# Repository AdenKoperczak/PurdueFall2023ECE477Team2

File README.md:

# PurdueFall2023ECE477Team2
Code and other files for a desktop Skee-Ball Machine. Our team website can be
found at [https://engineering.purdue.edu/477grp2/](https://engineering.purdue.edu/477grp2/).

# Purdue ECE47700 - Digital Systems Senior Project
This class involves designing a electronics project that could be sold as a 
product. Such a product must involve either a microcontroller or FPGA. More
information can be found at [https://engineering.purdue.edu/ece477/](https://engineering.purdue.edu/ece477/).

# Git Folders and Files
The files in our Git Repository can be broken into two sections: electrical and
code. Electrical design was done in KiCAD 7.0 and includes both schematics and
PCB layouts. Code was done using SystemWorkbench. There are also some other 
code and support files. Bellow is a description of each folder and what it
contains along with some soport files files.

## General Files
- Used Resources.txt: This contains what parts of the microcontroller are being
                      used for what.

## Electrical
- Audio AMP: Contains initial design for our audio amplifier.
- Schematic: Contains the overall schematic and PCB for our design.
- power control: Contains the initial design for our power circuitry.
- sensor: Contains the initial design for our laser break circuit.

## Microcontroller Code
- HUB75Lib: This contains a library and test code to run a 32x64 HUB75 display
            including a font library.
- WS2812BLib: This contains a library and test code for running a WS2812B LED strip.
- SoundLib: This contains a library and test code for generating and playing audio.

## Other Code
- HUB75Font\_Generate: This contains code for generating a font library for the
                       HUB75Lib.

# Project Description
Our project aims to rekindle the nostalgic joy of the traditional Skee-Ball game while
incorporating cutting-edge technology for an enhanced playing experience in the form of
game modes, normal, time attack, and streak. The normal game mode is the same 
as the traditional skate-ball game mode, such that a player would get nine balls and attempt
to score the highest score possible at their own pace, for which the scores per ball are
simply added to get the final score. After they run out of nine balls, any ball they try
to score after would not count, as the game would be over. In time attack mode, the
player sets a time (up to 5 minutes) with an unlimited ball count to score as high as
possible. For the streak mode, the player gets an "unlimited" number of balls as long as
as they score 20 points or higher on the current shot; Once they miss the shot, the score
is finalized. Finally, the timed streak mode combines the time attack with a score.
multiplier, which will go up by 0.1x from 1x every time they make the shot, maxing out at
1.5x and indicated by an LED light bar to the player. Once the player misses a 20+
point shot, the multiplier is reset. The Skee-Ball Machine" is similar to other arcade
machines that you can easily see in arcades; however, they are unaffordable to buy and
are huge in size. Therefore, we specifically designed it to be portable and affordable. 
To make it portable, we replaced the rolling rail into bouncing pad, so the player will 
score the ball by throwing the ball off of the bouncing pad. This device will use a microcontroller,
along with several sensors, buttons, displays, and a speaker to make an iterative game with
different scoring modes to keep the game fresh. In detail, sensors will detect the ball
once they are scored. Also, there will be a speaker, so it will have certain game effects.
sounds when scored through a user-defined amplifier. Also, there will be a display for user 
interfaces to show the score and how much time is left. Finally, we will create a power regulator
to regulate the power supply. We will use a commercial 12V power supply because our speaker 
requires 12V, then we will implement a voltage regulator (buck converter) from 12V commercial 
voltage input to 5V to supply our display, and another linear regulator from 5V to 3.3V to 
supply microprocessors and other components.

## Stretch Goal:
An ability to implement a WS2812B LED-strip to generate some flashing light as a game effect, 
using GPIO pins to operate and a PWM to adjust brightness and frequency to generate certain effect.

## Project Specific Design Requirements (PSDRs):
- PSDR #1 (Hardware): An ability to implement one 32-by-64 column-row
                      matrix display to interface with user, by communicating through GPIO
                      pins from microcontroller. 
- PSDR #2 (Hardware): An ability to implement one 4-by-4 column-row
                      matrix keypad to receive user's input, by communicating through GPIO
                      pins from microcontroller.
- PSDR #3 (Hardware): An ability to generate a soundwave using DAC 
                      from microcontroller and amplify the signal using a user designed
                      audio amplifier to play game effect sounds through a speaker.
- PSDR #4 (Hardware): An ability to implement a step down voltage
                      regulator(buck converter) from 12V commercial voltage input to 5V, and
                      another linear regulator from 5V to 3.3V as we need both 5V and 3.3V
                      to supply different components.
- PSDR #5 (Software): An ability to implement the game logic using system
                      workbench for STM32(eclipse), to properly implement all components, such
                      as optical sensor, display, keypad, and speaker.

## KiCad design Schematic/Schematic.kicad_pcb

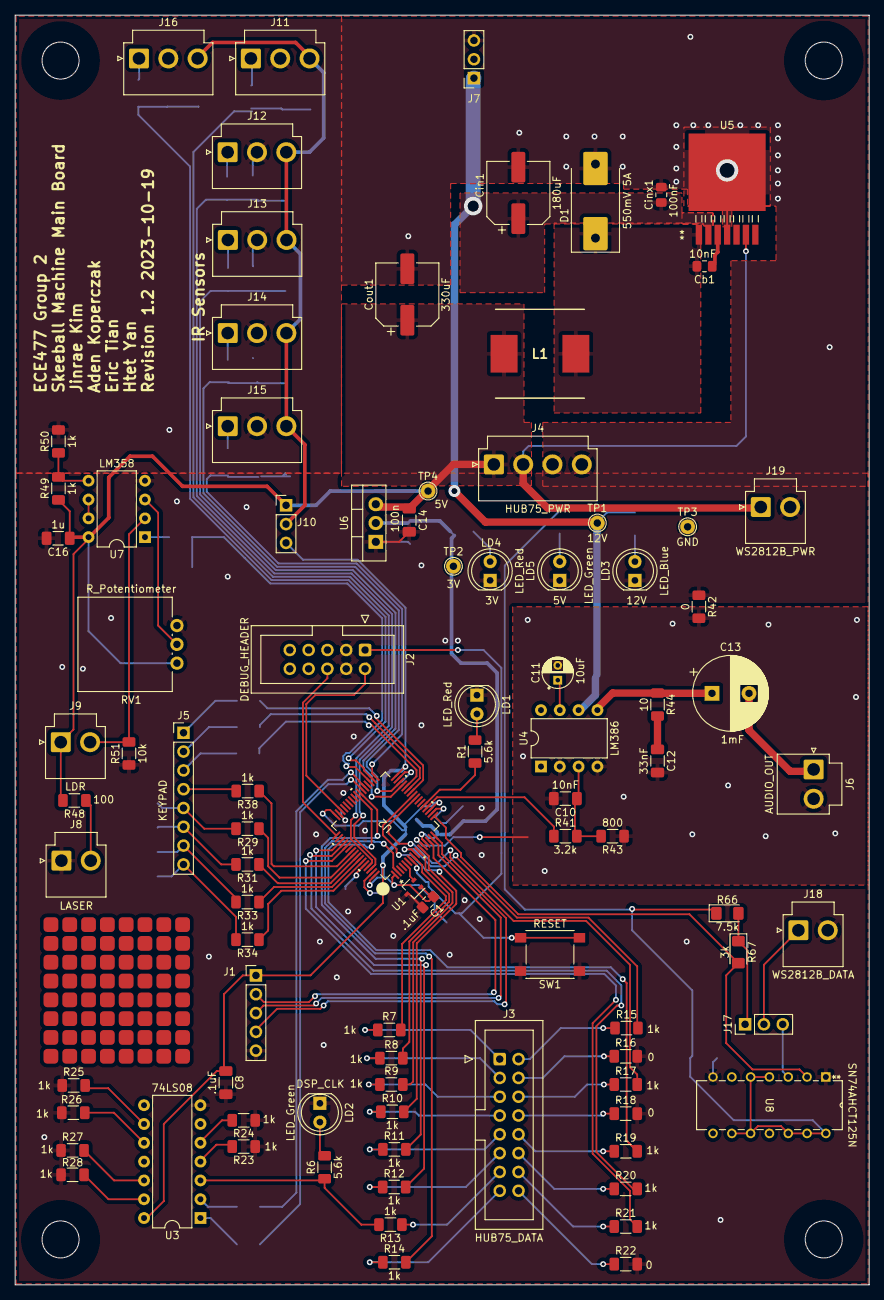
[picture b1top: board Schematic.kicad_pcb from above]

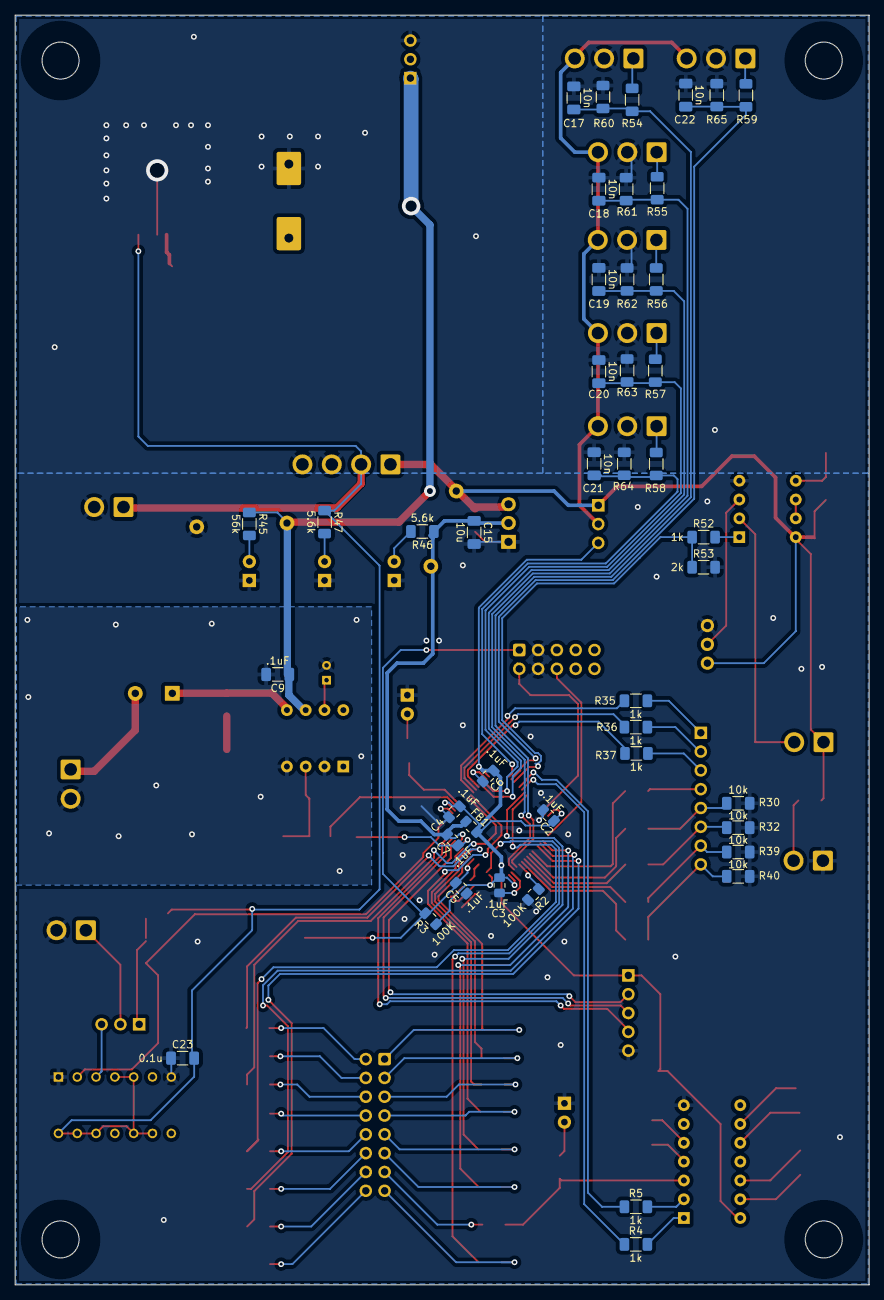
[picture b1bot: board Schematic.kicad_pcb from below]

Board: 2 copper layers, 115.3 x 171.4 mm, 139 parts (44 on the bottom side), 107 nets.

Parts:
C1, C2, C3, C4, C5, C6, C7: .1uF; C_0805_2012Metric_Pad1.18x1.45mm_HandSolder
C8, C9: .1uF; C_1206_3216Metric_Pad1.33x1.80mm_HandSolder
C10: 10nF; C_1206_3216Metric_Pad1.33x1.80mm_HandSolder
C11: 10uF; CP_Radial_D4.0mm_P2.00mm
C12: 33nF; C_1206_3216Metric_Pad1.33x1.80mm_HandSolder
C13: 1mF; CP_Radial_D10.0mm_P5.00mm
C14: 100n; C_1206_3216Metric_Pad1.33x1.80mm_HandSolder
C15: 10u; C_1206_3216Metric_Pad1.33x1.80mm_HandSolder
C16: 1u; C_1206_3216Metric_Pad1.33x1.80mm_HandSolder
C17, C18, C19, C20, C21, C22: 10n; C_1206_3216Metric_Pad1.33x1.80mm_HandSolder
C23: 0.1u; C_1206_3216Metric_Pad1.33x1.80mm_HandSolder
Cb1: 10nF; C_0805_2012Metric_Pad1.18x1.45mm_HandSolder
Cin1: 180uF; CP_Elec_8x6.9
Cinx1: 100nF; C_0805_2012Metric_Pad1.18x1.45mm_HandSolder
Cout1: 330uF; CP_Elec_8x6.9
D1: 550mV 5A; D_SMC-RM10_Universal_Handsoldering
FB1: Ferrite Bead; L_0805_2012Metric_Pad1.15x1.40mm_HandSolder
H1, H2, H3, H4: MountingHole; MountingHole_5mm
J1: Conn_01x05_Pin; PinHeader_1x05_P2.54mm_Vertical
J2: DEBUG_HEADER; IDC-Header_2x05_P2.54mm_Vertical
J3: HUB75_DATA; IDC-Header_2x08_P2.54mm_Vertical
J4: HUB75_PWR; JST_VH_B4P-VH-B_1x04_P3.96mm_Vertical
J5: KEYPAD; PinHeader_1x08_P2.54mm_Vertical
J6: AUDIO_OUT; JST_VH_B2P-VH-B_1x02_P3.96mm_Vertical
J7: Conn_01x03_Pin; PinSocket_1x03_P2.54mm_Vertical
J8: LASER; JST_VH_B2P-VH-B_1x02_P3.96mm_Vertical
J9: LDR; JST_VH_B2P-VH-B_1x02_P3.96mm_Vertical
J10, J17: Conn_01x03_Pin; PinHeader_1x03_P2.54mm_Vertical
J11, J12, J13, J14, J15, J16: Conn_01x03_Pin; JST_VH_B3P-VH_1x03_P3.96mm_Vertical
J18: WS2812B_DATA; JST_VH_B2P-VH-B_1x02_P3.96mm_Vertical
J19: WS2812B_PWR; JST_VH_B2P-VH-B_1x02_P3.96mm_Vertical
L1: 10uH; INDPM120120X1020N
LD1, LD4: LED_Red; LED_D5.0mm
LD2, LD5: LED_Green; LED_D5.0mm
LD3: LED_Blue; LED_D5.0mm
R1, R6, R46, R47: 5.6k; R_1206_3216Metric_Pad1.30x1.75mm_HandSolder
R2, R3: 100K; C_0805_2012Metric_Pad1.18x1.45mm_HandSolder
R4, R5, R7, R8, R9, R10, R11, R12, R13, R14, R15, R17, R19, R20, R21, R23, R24, R25, R26, R27, R28, R29, R31, R33, R34, R35, R36, R37, R38, R49, R50, R52, R54, R55, R56, R57, R58, R59: 1k; R_1206_3216Metric_Pad1.30x1.75mm_HandSolder
R16, R18, R22, R42: 0; R_1206_3216Metric_Pad1.30x1.75mm_HandSolder
R30, R32, R39, R40, R51: 10k; R_1206_3216Metric_Pad1.30x1.75mm_HandSolder
R41: 3.2k; R_1206_3216Metric_Pad1.30x1.75mm_HandSolder
R43: 800; R_1206_3216Metric_Pad1.30x1.75mm_HandSolder
R44: 10; R_1206_3216Metric_Pad1.30x1.75mm_HandSolder
R45: 56k; R_1206_3216Metric_Pad1.30x1.75mm_HandSolder
R48: 100; R_1206_3216Metric_Pad1.30x1.75mm_HandSolder
R53, R60, R61, R62, R63, R64, R65: 2k; R_1206_3216Metric_Pad1.30x1.75mm_HandSolder
R66: 7.5k; LED_1206_3216Metric_Pad1.42x1.75mm_HandSolder
R67: 3k; LED_1206_3216Metric_Pad1.42x1.75mm_HandSolder
RV1: R_Potentiometer; Potentiometer_Vishay_148-149_Single_Vertical
SW1: RESET; SW_SPST_PTS645
TP1: 12V; TestPoint_THTPad_D2.0mm_Drill1.0mm
TP2: 3V; TestPoint_THTPad_D2.0mm_Drill1.0mm
TP3: GND; TestPoint_THTPad_D2.0mm_Drill1.0mm
TP4: 5V; TestPoint_THTPad_D2.0mm_Drill1.0mm
U1: MAX7375AXR805; SOT-323_SC-70
U2: STM32F091RCT6; LQFP64-10x10mm_STM
U3: 74LS08; DIP-14_W7.62mm
U4: LM386; DIP-8_W7.62mm
U5: LM2678S-12; TS7B
U6: LD1117S33TR_SOT223; TO-220-3_Vertical
U7: LM358; DIP-8_W7.62mm
U8: SN74AHCT125N; N14

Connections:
+3V0: C1.1, C2.1, C3.1, C4.1, C6.1, C8.1, FB1.2, J1.1, J10.3, R3.1, U1.1 (V+), U2.1 (VBAT), U2.19 (VDD), U2.32 (VDD), U2.48 (VDDIO2), U2.64 (VDD), U3.14 (VCC)
+5V: C14.1, C16.1, C23.2, Cout1.1, J4.1, J4.2, J9.1, J10.1, J19.1, L1.2, R47.1, R48.2, R49.1, R66.1, RV1.3, TP4.1, U5.6 (FB), U6.3 (VI), U7.8 (V+), U8.4 (*2OE), U8.5 (2A), U8.9 (3A), U8.10 (*3OE), U8.12 (4A), U8.13 (*4OE), U8.14 (VCC)
+12V: C9.1, Cin1.1, Cinx1.1, J7.1, R45.1, TP1.1, U4.6 (V+), U5.2 (VIN)
/Sensors/Vsens: J10.2, J11.3, J12.3, J13.3, J14.3, J15.3, J16.3
/WS2812B/WS_DATA_RES: J17.1, R66.2, R67.1
/WS2812B/WS_DATA_SHIFTER: J17.3, U8.3 (1Y)
/microprocessor/BOOT0: R2.1, U2.60 (PF11-BOOT0)
/microprocessor/NRST: C5.1, J2.1, R3.2, SW1.2, U2.7 (NRST)
/microprocessor/SWCLK_IN: J2.6, U2.49 (PA14)
/microprocessor/SWDIO_IN: J2.2, U2.46 (PA13)
/power/VSW: Cb1.2, D1.1 (K), L1.1, U5.1 (VSW)
GND: C1.2, C2.2, C3.2, C4.2, C5.2, C6.2, C8.2, C14.2, C15.2, C16.2, C17.2, C18.2, C19.2, C20.2, C21.2, C22.2, C23.1, Cin1.2, Cinx1.2, Cout1.2, D1.2 (A), J1.5, J2.3, J2.4, J4.3, J4.4, J7.3, J8.1, J11.2, J12.2, J13.2, J14.2, J15.2, J16.2, J18.2, J19.2, LD1.1 (K), LD2.1 (K), LD3.1 (K), LD4.1 (K), LD5.1 (K), R2.2, R16.2, R18.2, R22.2, R23.1, R24.1, R25.1, R26.1, R27.1, R28.1, R30.1, R32.1, R39.1, R40.1, R42.1, R50.2, R51.1, R53.2, R60.2, R61.2, R62.2, R63.2, R64.2, R65.2, RV1.1, SW1.1, TP3.1, U1.3 (GND), U2.18 (VSS), U2.31 (VSS), U2.47 (VSS), U2.63 (VSS), U3.7 (GND), U5.4 (GND), U5.8 (TAB), U6.1 (GND), U7.4 (V-), U8.1 (*1OE), U8.7 (GND)
GNDA: C7.2, C9.2, C10.2, C11.2, C12.2, J6.2, R42.2, R43.1, U2.12 (VSSA), U4.2 (-), U4.4 (GND)
unnamed: C12.1, R44.2
unnamed: C13.1, R44.1, U4.5
unnamed: J3.1, R7.1
unnamed: J3.2, R15.1
unnamed: J3.3, R8.1
unnamed: J3.4, R16.1
unnamed: J3.5, R9.1
unnamed: J3.6, R17.1
unnamed: J3.7, R10.1
unnamed: J3.8, R18.1
unnamed: J3.9, R11.1
unnamed: J3.10, R19.1
unnamed: J3.11, R12.1
unnamed: J3.12, R20.1
unnamed: J3.13, R13.1
unnamed: J3.14, R21.1
unnamed: J3.15, R14.1
unnamed: J3.16, R22.1
unnamed: J5.1, R35.2
unnamed: J5.2, R36.2
unnamed: J5.3, R37.2
unnamed: J5.4, R38.2
unnamed: J5.5, R29.2, R30.2
unnamed: J5.6, R31.2, R32.2
unnamed: J5.7, R33.2, R39.2
unnamed: J5.8, R34.2, R40.2
unnamed: C13.2, J6.1
unnamed: J8.2, R48.1
unnamed: J9.2, R51.2, U7.2 (-)
unnamed: J11.1, R54.2
unnamed: J12.1, R55.2
unnamed: J13.1, R56.2
unnamed: J14.1, R57.2
unnamed: J15.1, R58.2
unnamed: J16.1, R59.2
unnamed: J17.2, J18.1
unnamed: LD1.2 (A), R1.2
unnamed: LD2.2 (A), R6.2
unnamed: LD3.2 (A), R45.2
unnamed: LD4.2 (A), R46.2
unnamed: LD5.2 (A), R47.2
unnamed: R4.2, U3.1
unnamed: R5.2, U3.2
unnamed: R6.1, R13.2, U3.3
unnamed: R23.2, U3.4
unnamed: R24.2, U3.5
unnamed: R25.2, U3.9
unnamed: R26.2, U3.10
unnamed: R27.2, U3.12
unnamed: R28.2, U3.13
unnamed: R52.2, U7.1
unnamed: U1.2 (CLOCK), U2.5 (PF0-OSC_IN)
unnamed: R1.1, U2.21 (PA5)
unnamed: C10.1, R41.2, R43.2, U4.3 (+)
unnamed: C11.1, U4.7 (BYPASS)
unnamed: Cb1.1, U5.3 (CB)
unnamed: RV1.2, U7.3 (+)
unnamed: R49.2, R50.1, U7.5 (+)
unnamed: U7.6 (-), U7.7
PA0: J1.2, U2.14 (PA0)
PA1: J1.3, U2.15 (PA1)
PA2: J1.4, U2.16 (PA2)
PA3: R67.2, U2.17 (PA3), U8.2 (1A)
PA4: R41.1, U2.20 (PA4)
PB0: R35.1, U2.26 (PB0)
PB1: R36.1, U2.27 (PB1)
PB2: R37.1, U2.28 (PB2)
PB3: R38.1, U2.55 (PB3)
PB4: R29.1, U2.56 (PB4)
PB5: R31.1, U2.57 (PB5)
PB6: R33.1, U2.58 (PB6)
PB7: R34.1, U2.59 (PB7)
PB8: C17.1, R54.1, R60.1, U2.61 (PB8)
PB9: C18.1, R55.1, R61.1, U2.62 (PB9)
PB10: C19.1, R56.1, R62.1, U2.29 (PB10)
PB11: C20.1, R57.1, R63.1, U2.30 (PB11)
PB12: C21.1, R58.1, R64.1, U2.33 (PB12)
PB13: C22.1, R59.1, R65.1, U2.34 (PB13)
PB14: R52.1, R53.1, U2.35 (PB14)
PC0: R7.2, U2.8 (PC0)
PC1: R15.2, U2.9 (PC1)
PC2: R8.2, U2.10 (PC2)
PC3: R9.2, U2.11 (PC3)
PC4: R17.2, U2.24 (PC4)
PC5: R10.2, U2.25 (PC5)
PC6: R5.1, U2.37 (PC6)
PC7: R4.1, U2.38 (PC7)
PC8: R11.2, U2.39 (PC8)
PC9: R19.2, U2.40 (PC9)
PC10: R12.2, U2.51 (PC10)
PC11: R20.2, U2.52 (PC11)
PC12: R21.2, U2.53 (PC12)
PC13: R14.2, U2.2 (PC13)
Vin: C7.1, C15.1, FB1.1, R46.1, TP2.1, U2.13 (VDDA), U6.2 (VO)

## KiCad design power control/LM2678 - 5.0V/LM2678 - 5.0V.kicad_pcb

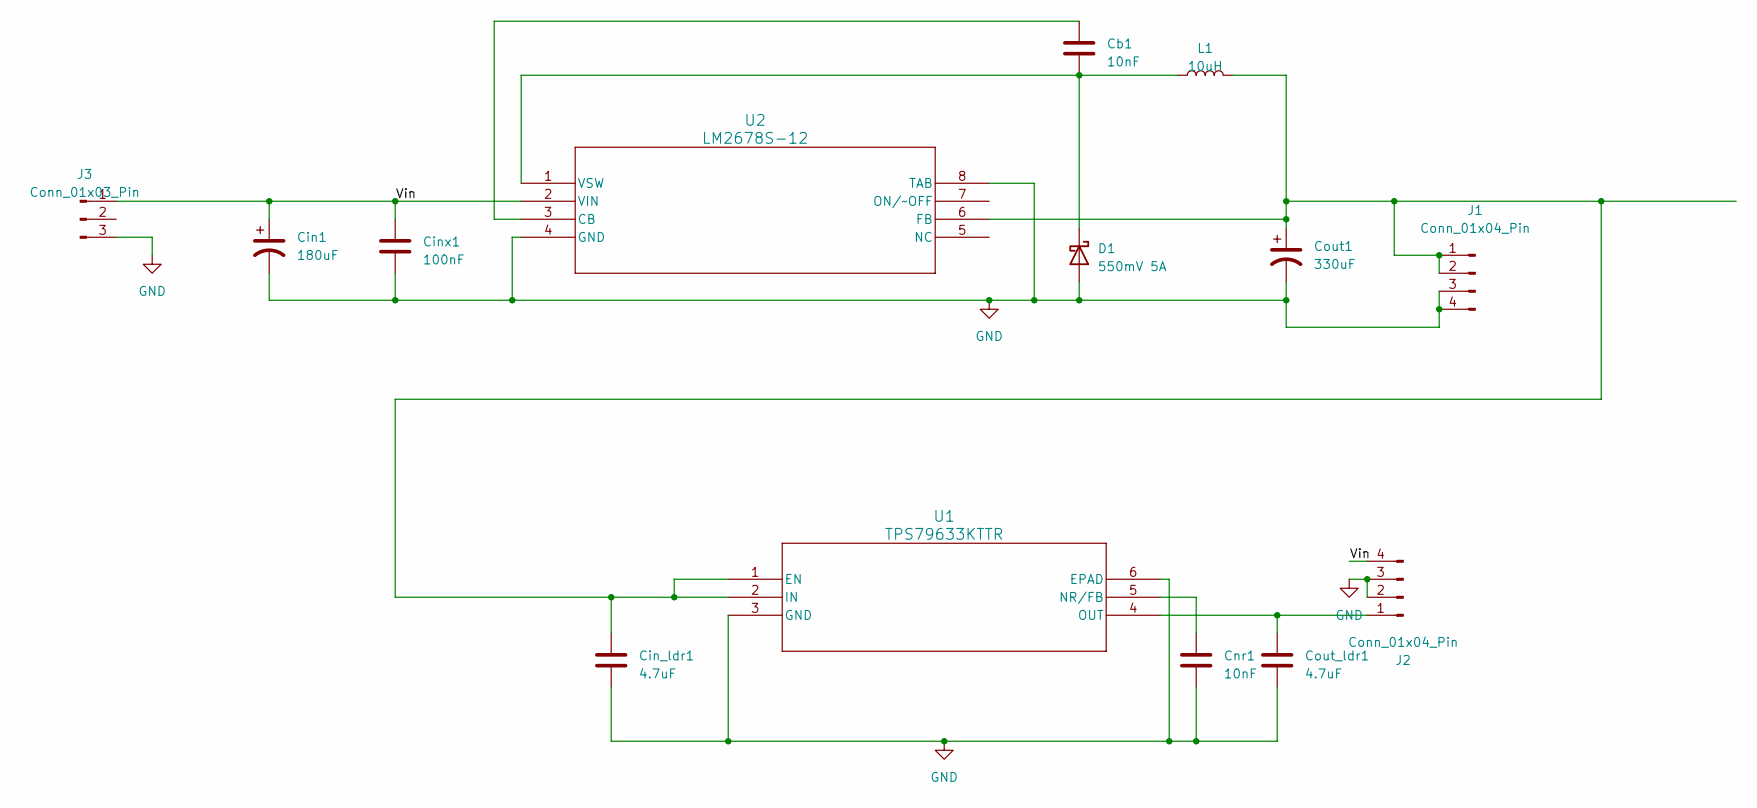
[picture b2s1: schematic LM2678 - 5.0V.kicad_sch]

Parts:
Cb1: 10nF; C_0805_2012Metric_Pad1.18x1.45mm_HandSolder
Cin1: 180uF; CP_Elec_8x6.9
Cin_ldr1: 4.7uF; C_0805_2012Metric_Pad1.18x1.45mm_HandSolder
Cinx1: 100nF; C_0805_2012Metric_Pad1.18x1.45mm_HandSolder
Cnr1: 10nF; C_0805_2012Metric_Pad1.18x1.45mm_HandSolder
Cout1: 330uF; CP_Elec_8x6.9
Cout_ldr1: 4.7uF; C_0805_2012Metric_Pad1.18x1.45mm_HandSolder
D1: 550mV 5A; D_SMC-RM10_Universal_Handsoldering
J1, J2: Conn_01x04_Pin; JST_VH_B4P-VH-B_1x04_P3.96mm_Vertical
J3: Conn_01x03_Pin; PinHeader_1x03_P2.54mm_Vertical
L1: 10uH; INDPM120120X1020N
U1: TPS79633KTTR; KTT5_6P22X6P86_TEX
U2: LM2678S-12; TS7B

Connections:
/Vin: Cin1.1, Cinx1.1, J2.4, J3.1, U2.2 (VIN)
GND: Cin1.2, Cin_ldr1.2, Cinx1.2, Cnr1.2, Cout1.2, Cout_ldr1.2, D1.2 (A), J1.3, J1.4, J2.2, J2.3, J3.3, U1.3 (GND), U1.6 (EPAD), U2.4 (GND), U2.8 (TAB)
unnamed: Cb1.2, D1.1 (K), L1.1, U2.1 (VSW)
unnamed: Cin_ldr1.1, Cout1.1, J1.1, J1.2, L1.2, U1.1 (EN), U1.2 (IN), U2.6 (FB)
unnamed: Cout_ldr1.1, J2.1, U1.4 (OUT)
unnamed: Cnr1.1, U1.5 (NR/FB)
unnamed: Cb1.1, U2.3 (CB)

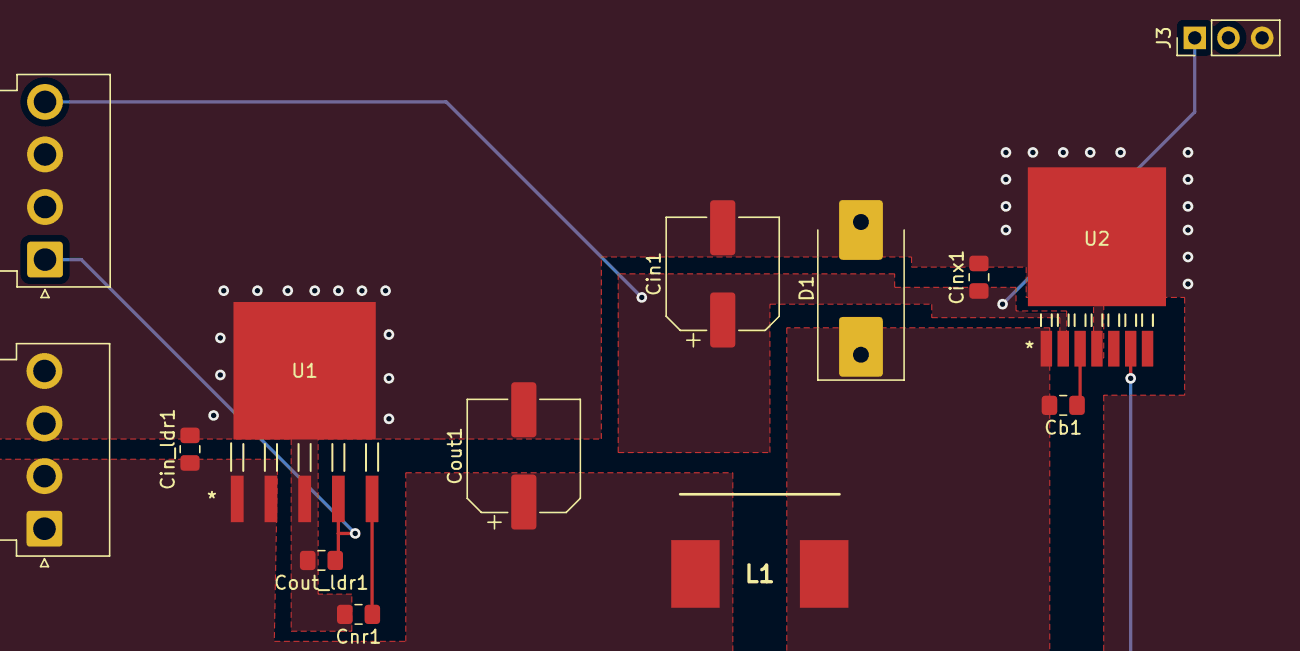
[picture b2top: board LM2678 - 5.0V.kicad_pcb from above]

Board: 2 copper layers, 14 parts (0 on the bottom side), 7 nets.

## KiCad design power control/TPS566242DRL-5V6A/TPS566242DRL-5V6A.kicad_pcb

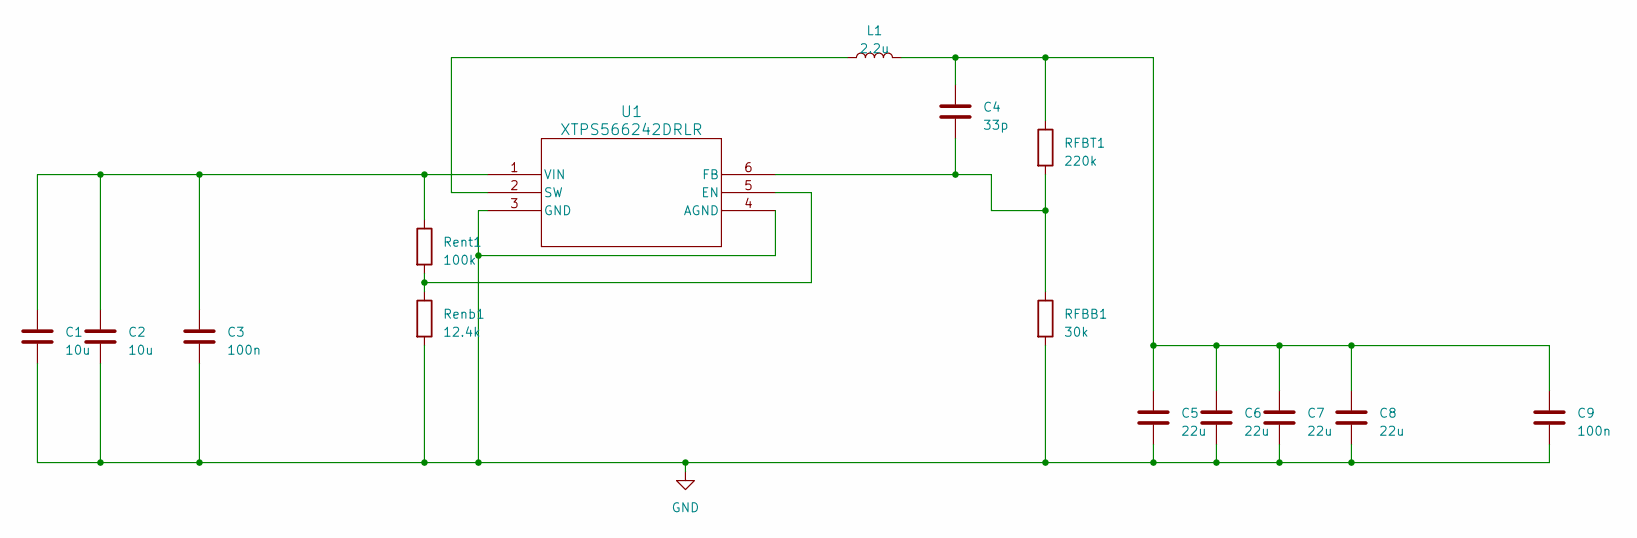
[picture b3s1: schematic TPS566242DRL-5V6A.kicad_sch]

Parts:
C1, C2: 10u; C_0805_2012Metric_Pad1.18x1.45mm_HandSolder
C3, C9: 100n; C_0603_1608Metric_Pad1.08x0.95mm_HandSolder
C4: 33p; C_0402_1005Metric_Pad0.74x0.62mm_HandSolder
C5, C6, C7, C8: 22u; C_0805_2012Metric_Pad1.18x1.45mm_HandSolder
L1: 2.2u; L_Coilcraft_XAL5030-XXX
RFBB1: 30k; R_0603_1608Metric_Pad0.98x0.95mm_HandSolder
RFBT1: 220k; R_0603_1608Metric_Pad0.98x0.95mm_HandSolder
Renb1: 12.4k; R_0402_1005Metric_Pad0.72x0.64mm_HandSolder
Rent1: 100k; R_0402_1005Metric_Pad0.72x0.64mm_HandSolder
U1: XTPS566242DRLR; SOT6_DRL_TEX

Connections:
GND: C1.2, C2.2, C3.2, C5.2, C6.2, C7.2, C8.2, C9.2, RFBB1.2, Renb1.2, U1.3 (GND), U1.4 (AGND)
unnamed: C4.1, C5.1, C6.1, C7.1, C8.1, C9.1, L1.2, RFBT1.1
unnamed: Renb1.1, Rent1.2, U1.5 (EN)
unnamed: C4.2, RFBB1.1, RFBT1.2, U1.6 (FB)
unnamed: L1.1, U1.2 (SW)
unnamed: C1.1, C2.1, C3.1, Rent1.1, U1.1 (VIN)

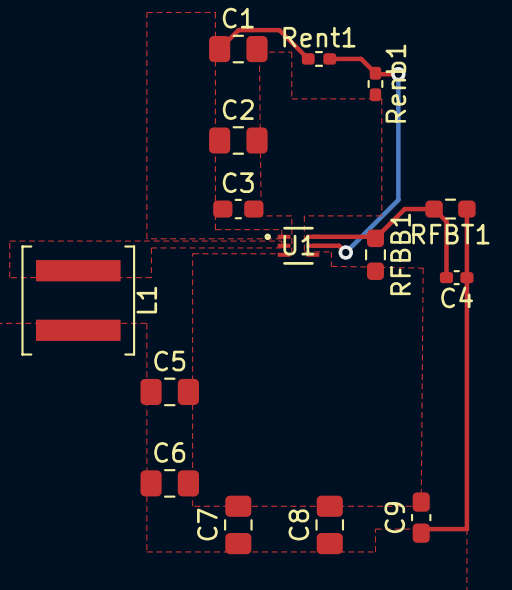
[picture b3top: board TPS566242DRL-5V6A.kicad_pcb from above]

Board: 2 copper layers, 15 parts (0 on the bottom side), 6 nets.

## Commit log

2023-09-06 Inital HUB75 Code
2023-09-06 Added .gitignore (now only vim .swp files)
2023-09-06 Added 'User Resources.txt'. Explaines what portions of the Microcontroller we have used, and are likely to use.
2023-09-14 added code for workflow to make fonts, along with a subsection of a font (A-Z, 0-9, '-', ':', '.')
2023-09-14 Updated 'Used Resources.txt'
2023-09-14 changed font size to 7x5, implemented fix for direction of font rendering, implemented fix for suboptimal brigtness.
2023-09-25 Added schematic and imported microcontroller symble and footprint
2023-09-26 Added Schematic Backups to gitignore
2023-09-26 Added paritial schematic including microprocessor, hub75 and keypad
2023-09-26 updated schematic overall view
2023-09-26 Added power supply.
2023-09-27 Added audio circuitry
2023-09-29 fixed power circuit
2023-10-03 modified power control to remove old regulator
2023-10-03 initial CB design
2023-10-03 Most of the schematic and PCB layout.
2023-10-04 Added stuff from today
2023-10-05 Added sensors. Fixed other stuff.
2023-10-07 initially added sensors.
2023-10-07 Mostly finallized PCB
2023-10-10 Added images
2023-10-10 IDK if anything acutally changed
2023-10-12 Added Cap to osilator, and fixed posible issues with signals near it.
2023-10-12 fixed exporting script
2023-10-12 Updated svg's
2023-10-13 Implemented some suggestions from presentation. Power trace size, reset button position, mounting holes, copper fill near edge, WS Data moved, removed debuge LED and analog vias.
2023-10-13 Forgot to save the schematic from the last commit.
2023-10-18 Lab fixes
2023-10-19 Added level shifter (may or may not use) other minor fixes
2023-10-19 relabeld all of the components so they have more resonable numbers
2023-10-20 fixed LM385 not having voltage div, and ploted plots.
2023-10-21 Create keypad
2023-10-22 updated Used Resources
2023-10-22 Added WS2812BLib and fixed some issues with Used Resources.txt
2023-10-28 Create keypad1
    asdf
2023-10-28 keypad
2023-10-28 Rename main (3).c to keypad.c
2023-11-02 Updated ws2812b lib
2023-11-02 Added SoundLib
2023-11-02 began interation. Both HUB75 and Sound working
2023-11-08 Update keypad.c
    need to swap pb0-3 and pb4-7
2023-11-08 modified keypad.c to work on with lower pins as inputs.
2023-11-08 added working keypad code to integration
2023-11-08 moved over to non pull method for screen update
2023-11-08 changed keypad timing for better debouncing
2023-11-10 added sensor code, started on some game logic
2023-11-10 finished integrating sensors
2023-11-10 Working Normal and Time Attack modes with display and sensors.
2023-11-14 Change some names, updated scoring.
2023-11-30 Fixed font, fixed some issues with ws2812b, finished implementation
2023-12-06 few minor additions such as mute, soft power off, and replay. Fixed interupt priority.
